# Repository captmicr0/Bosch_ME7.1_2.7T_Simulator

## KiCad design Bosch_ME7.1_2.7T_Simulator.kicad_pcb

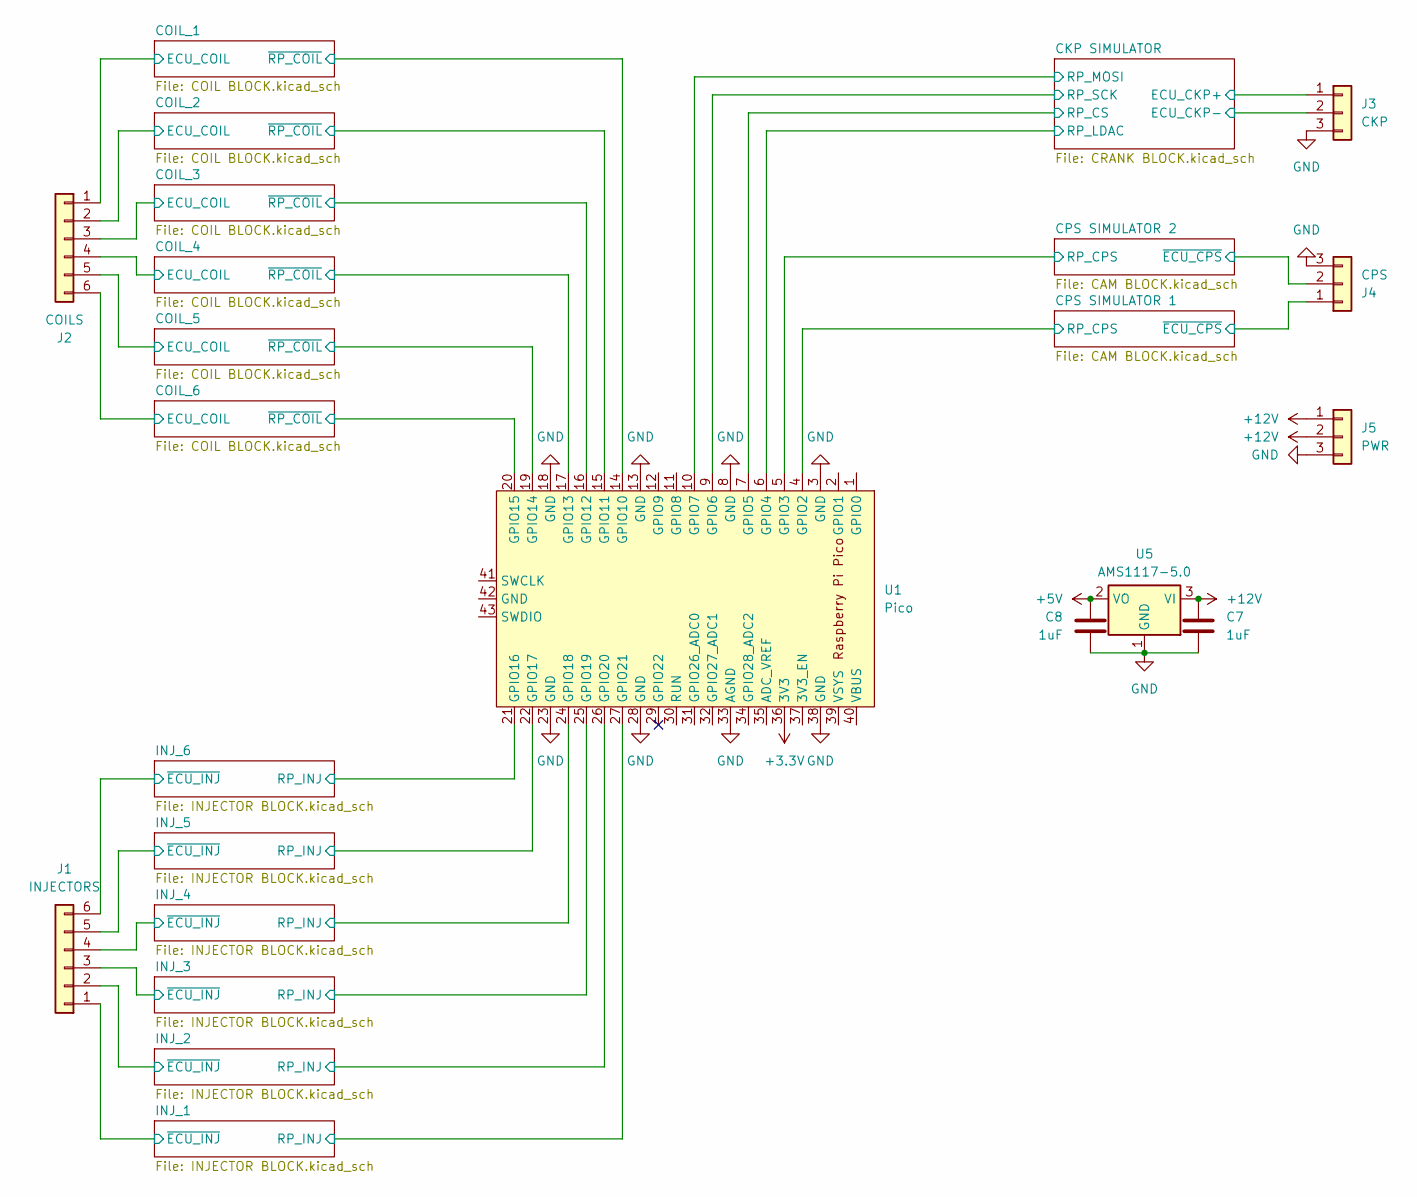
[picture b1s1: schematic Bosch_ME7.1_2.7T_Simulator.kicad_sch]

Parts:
C7, C8: 1uF; C_0603_1608Metric
J1: INJECTORS; JST_XH_B6B-XH-AM_1x06_P2.50mm_Vertical
J2: COILS; JST_XH_B6B-XH-AM_1x06_P2.50mm_Vertical
J3: CKP; JST_XH_B3B-XH-AM_1x03_P2.50mm_Vertical
J4: CPS; JST_XH_B3B-XH-AM_1x03_P2.50mm_Vertical
J5: PWR; JST_XH_B3B-XH-AM_1x03_P2.50mm_Vertical
U1: Pico; RPi_Pico_SMD_TH
U5: AMS1117-5.0; SOT-223-3_TabPin2

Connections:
+3.3V: U1.36 (3V3); also elsewhere on the board
+5V: C8.1, U5.2 (VO); also elsewhere on the board
+12V: C7.1, J5.1, J5.2, U5.3 (VI); also elsewhere on the board
/CKP SIMULATOR/ECU_CKP+: J3.1; also elsewhere on the board
/CKP SIMULATOR/ECU_CKP-: J3.2; also elsewhere on the board
/CKP SIMULATOR/RP_CS: U1.7 (GPIO5); also elsewhere on the board
/CKP SIMULATOR/RP_LDAC: U1.6 (GPIO4); also elsewhere on the board
/CKP SIMULATOR/RP_MOSI: U1.10 (GPIO7); also elsewhere on the board
/CKP SIMULATOR/RP_SCK: U1.9 (GPIO6); also elsewhere on the board
/COIL_1/ECU_COIL: J2.1; also elsewhere on the board
/COIL_1/~RP_COIL: U1.14 (GPIO10); also elsewhere on the board
/COIL_2/ECU_COIL: J2.2; also elsewhere on the board
/COIL_2/~RP_COIL: U1.15 (GPIO11); also elsewhere on the board
/COIL_3/ECU_COIL: J2.3; also elsewhere on the board
/COIL_3/~RP_COIL: U1.16 (GPIO12); also elsewhere on the board
/COIL_4/ECU_COIL: J2.4; also elsewhere on the board
/COIL_4/~RP_COIL: U1.17 (GPIO13); also elsewhere on the board
/COIL_5/ECU_COIL: J2.5; also elsewhere on the board
/COIL_5/~RP_COIL: U1.19 (GPIO14); also elsewhere on the board
/COIL_6/ECU_COIL: J2.6; also elsewhere on the board
/COIL_6/~RP_COIL: U1.20 (GPIO15); also elsewhere on the board
/CPS SIMULATOR 1/RP_CPS: U1.4 (GPIO2); also elsewhere on the board
/CPS SIMULATOR 1/~ECU_CPS: J4.1; also elsewhere on the board
/CPS SIMULATOR 2/RP_CPS: U1.5 (GPIO3); also elsewhere on the board
/CPS SIMULATOR 2/~ECU_CPS: J4.2; also elsewhere on the board
/INJ_1/RP_INJ: U1.27 (GPIO21); also elsewhere on the board
/INJ_1/~ECU_INJ: J1.1; also elsewhere on the board
/INJ_2/RP_INJ: U1.26 (GPIO20); also elsewhere on the board
/INJ_2/~ECU_INJ: J1.2; also elsewhere on the board
/INJ_3/RP_INJ: U1.25 (GPIO19); also elsewhere on the board
/INJ_3/~ECU_INJ: J1.3; also elsewhere on the board
/INJ_4/RP_INJ: U1.24 (GPIO18); also elsewhere on the board
/INJ_4/~ECU_INJ: J1.4; also elsewhere on the board
/INJ_5/RP_INJ: U1.22 (GPIO17); also elsewhere on the board
/INJ_5/~ECU_INJ: J1.5; also elsewhere on the board
/INJ_6/RP_INJ: U1.21 (GPIO16); also elsewhere on the board
/INJ_6/~ECU_INJ: J1.6; also elsewhere on the board
GND: C7.2, C8.2, J3.3, J4.3, J5.3, U1.3 (GND), U1.8 (GND), U1.13 (GND), U1.18 (GND), U1.23 (GND), U1.28 (GND), U1.33 (AGND), U1.38 (GND), U5.1 (GND); also elsewhere on the board

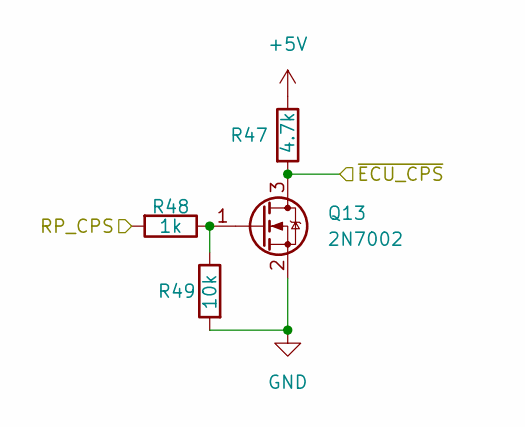
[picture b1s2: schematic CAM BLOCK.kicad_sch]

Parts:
Q13: 2N7002; SOT-23
R47: 4.7k; R_0603_1608Metric
R48: 1k; R_0603_1608Metric
R49: 10k; R_0603_1608Metric

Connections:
+5V: R47.1; also elsewhere on the board
/CPS SIMULATOR 1/RP_CPS: R48.2; also elsewhere on the board
/CPS SIMULATOR 1/~ECU_CPS: Q13.3 (D), R47.2; also elsewhere on the board
GND: Q13.2 (S), R49.2; also elsewhere on the board
unnamed: Q13.1 (G), R48.1, R49.1

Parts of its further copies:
Q14: 2N7002; SOT-23
R46: 4.7k; R_0603_1608Metric
R50: 1k; R_0603_1608Metric
R51: 10k; R_0603_1608Metric

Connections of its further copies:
+5V: R46.1; also elsewhere on the board
/CPS SIMULATOR 2/RP_CPS: R50.2; also elsewhere on the board
/CPS SIMULATOR 2/~ECU_CPS: Q14.3 (D), R46.2; also elsewhere on the board
GND: Q14.2 (S), R51.2; also elsewhere on the board
unnamed: Q14.1 (G), R50.1, R51.1

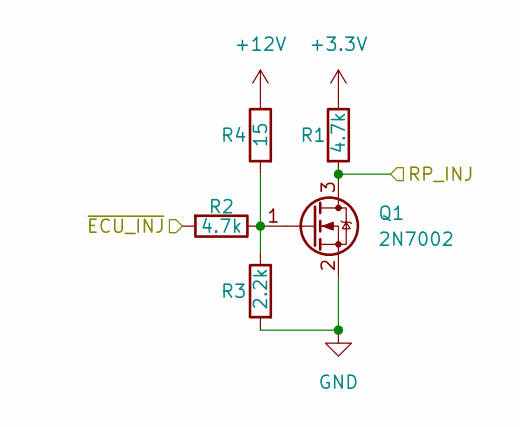
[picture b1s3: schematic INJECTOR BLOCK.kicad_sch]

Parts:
Q1: 2N7002; SOT-23
R1, R2: 4.7k; R_0603_1608Metric
R3: 2.2k; R_0603_1608Metric
R4: 15; JST_XH_B2B-XH-AM_1x02_P2.50mm_Vertical

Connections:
+3.3V: R1.1; also elsewhere on the board
+12V: R4.1; also elsewhere on the board
/INJ_1/RP_INJ: Q1.3 (D), R1.2; also elsewhere on the board
/INJ_1/~ECU_INJ: R2.2; also elsewhere on the board
GND: Q1.2 (S), R3.2; also elsewhere on the board
unnamed: Q1.1 (G), R2.1, R3.1, R4.2

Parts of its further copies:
Q4, Q6, Q8, Q10, Q12: 2N7002; SOT-23
R11, R18, R25, R32, R39: 15; JST_XH_B2B-XH-AM_1x02_P2.50mm_Vertical
R12, R13, R19, R20, R26, R27, R33, R34, R40, R41: 4.7k; R_0603_1608Metric
R14, R21, R28, R35, R42: 2.2k; R_0603_1608Metric

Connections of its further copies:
+3.3V: R12.1, R19.1, R26.1, R33.1, R40.1; also elsewhere on the board
+12V: R11.1, R18.1, R25.1, R32.1, R39.1; also elsewhere on the board
/INJ_2/RP_INJ: Q4.3 (D), R12.2; also elsewhere on the board
/INJ_2/~ECU_INJ: R13.2; also elsewhere on the board
/INJ_3/RP_INJ: Q6.3 (D), R19.2; also elsewhere on the board
/INJ_3/~ECU_INJ: R20.2; also elsewhere on the board
/INJ_4/RP_INJ: Q8.3 (D), R26.2; also elsewhere on the board
/INJ_4/~ECU_INJ: R27.2; also elsewhere on the board
/INJ_5/RP_INJ: Q10.3 (D), R33.2; also elsewhere on the board
/INJ_5/~ECU_INJ: R34.2; also elsewhere on the board
/INJ_6/RP_INJ: Q12.3 (D), R40.2; also elsewhere on the board
/INJ_6/~ECU_INJ: R41.2; also elsewhere on the board
GND: Q4.2 (S), Q6.2 (S), Q8.2 (S), Q10.2 (S), Q12.2 (S), R14.2, R21.2, R28.2, R35.2, R42.2; also elsewhere on the board
unnamed: Q4.1 (G), R11.2, R13.1, R14.1
unnamed: Q6.1 (G), R18.2, R20.1, R21.1
unnamed: Q8.1 (G), R25.2, R27.1, R28.1
unnamed: Q10.1 (G), R32.2, R34.1, R35.1
unnamed: Q12.1 (G), R39.2, R41.1, R42.1

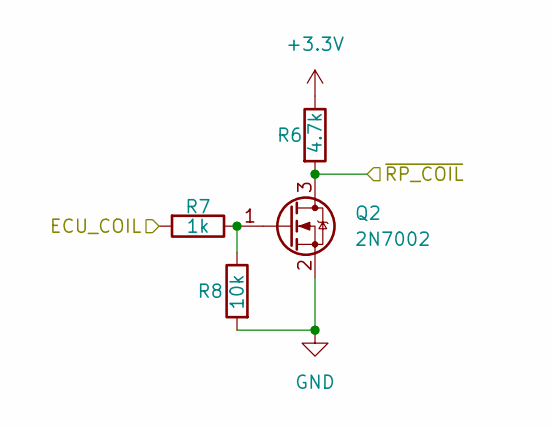
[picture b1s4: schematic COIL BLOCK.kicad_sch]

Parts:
Q2: 2N7002; SOT-23
R6: 4.7k; R_0603_1608Metric
R7: 1k; R_0603_1608Metric
R8: 10k; R_0603_1608Metric

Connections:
+3.3V: R6.1; also elsewhere on the board
/COIL_1/ECU_COIL: R7.2; also elsewhere on the board
/COIL_1/~RP_COIL: Q2.3 (D), R6.2; also elsewhere on the board
GND: Q2.2 (S), R8.2; also elsewhere on the board
unnamed: Q2.1 (G), R7.1, R8.1

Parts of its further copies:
Q3, Q5, Q7, Q9, Q11: 2N7002; SOT-23
R5, R15, R22, R29, R36: 4.7k; R_0603_1608Metric
R9, R16, R23, R30, R37: 1k; R_0603_1608Metric
R10, R17, R24, R31, R38: 10k; R_0603_1608Metric

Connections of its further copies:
+3.3V: R5.1, R15.1, R22.1, R29.1, R36.1; also elsewhere on the board
/COIL_2/ECU_COIL: R9.2; also elsewhere on the board
/COIL_2/~RP_COIL: Q3.3 (D), R5.2; also elsewhere on the board
/COIL_3/ECU_COIL: R16.2; also elsewhere on the board
/COIL_3/~RP_COIL: Q5.3 (D), R15.2; also elsewhere on the board
/COIL_4/ECU_COIL: R23.2; also elsewhere on the board
/COIL_4/~RP_COIL: Q7.3 (D), R22.2; also elsewhere on the board
/COIL_5/ECU_COIL: R30.2; also elsewhere on the board
/COIL_5/~RP_COIL: Q9.3 (D), R29.2; also elsewhere on the board
/COIL_6/ECU_COIL: R37.2; also elsewhere on the board
/COIL_6/~RP_COIL: Q11.3 (D), R36.2; also elsewhere on the board
GND: Q3.2 (S), Q5.2 (S), Q7.2 (S), Q9.2 (S), Q11.2 (S), R10.2, R17.2, R24.2, R31.2, R38.2; also elsewhere on the board
unnamed: Q3.1 (G), R9.1, R10.1
unnamed: Q5.1 (G), R16.1, R17.1
unnamed: Q7.1 (G), R23.1, R24.1
unnamed: Q9.1 (G), R30.1, R31.1
unnamed: Q11.1 (G), R37.1, R38.1

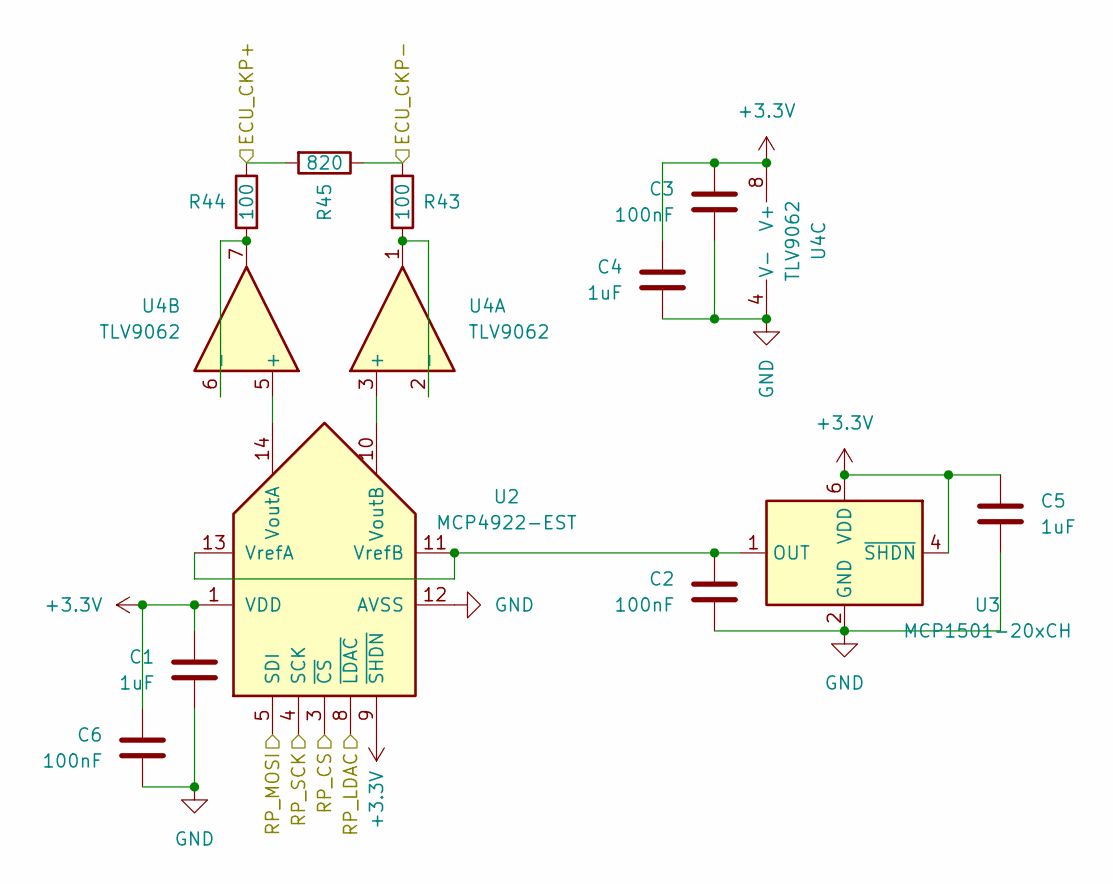
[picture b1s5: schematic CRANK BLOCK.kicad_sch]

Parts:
C1, C4, C5: 1uF; C_0603_1608Metric
C2, C3, C6: 100nF; C_0603_1608Metric
R43, R44: 100; R_0603_1608Metric
R45: 820; R_0603_1608Metric
U2: MCP4922-EST; TSSOP-14_4.4x5mm_P0.65mm
U3: MCP1501-20xCH; SOT-23-6
U4: TLV9062; TSSOP-8_4.4x3mm_P0.65mm

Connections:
+3.3V: C1.1, C3.1, C4.1, C5.1, C6.1, U2.1 (VDD), U2.9 (~SHDN), U3.4 (~SHDN), U3.6 (VDD), U4.8 (V+); also elsewhere on the board
/CKP SIMULATOR/ECU_CKP+: R44.1, R45.2; also elsewhere on the board
/CKP SIMULATOR/ECU_CKP-: R43.1, R45.1; also elsewhere on the board
/CKP SIMULATOR/RP_CS: U2.3 (~CS); also elsewhere on the board
/CKP SIMULATOR/RP_LDAC: U2.8 (~LDAC); also elsewhere on the board
/CKP SIMULATOR/RP_MOSI: U2.5 (SDI); also elsewhere on the board
/CKP SIMULATOR/RP_SCK: U2.4 (SCK); also elsewhere on the board
GND: C1.2, C2.2, C3.2, C4.2, C5.2, C6.2, U2.12 (AVSS), U3.2 (GND), U3.3 (GND), U3.5 (GND), U4.4 (V-); also elsewhere on the board
unnamed: U2.14 (VoutA), U4.5 (+)
unnamed: U2.10 (VoutB), U4.3 (+)
unnamed: C2.1, U2.11 (VrefB), U2.13 (VrefA), U3.1 (OUT)
unnamed: R43.2, U4.1, U4.2 (-)
unnamed: R44.2, U4.6 (-), U4.7

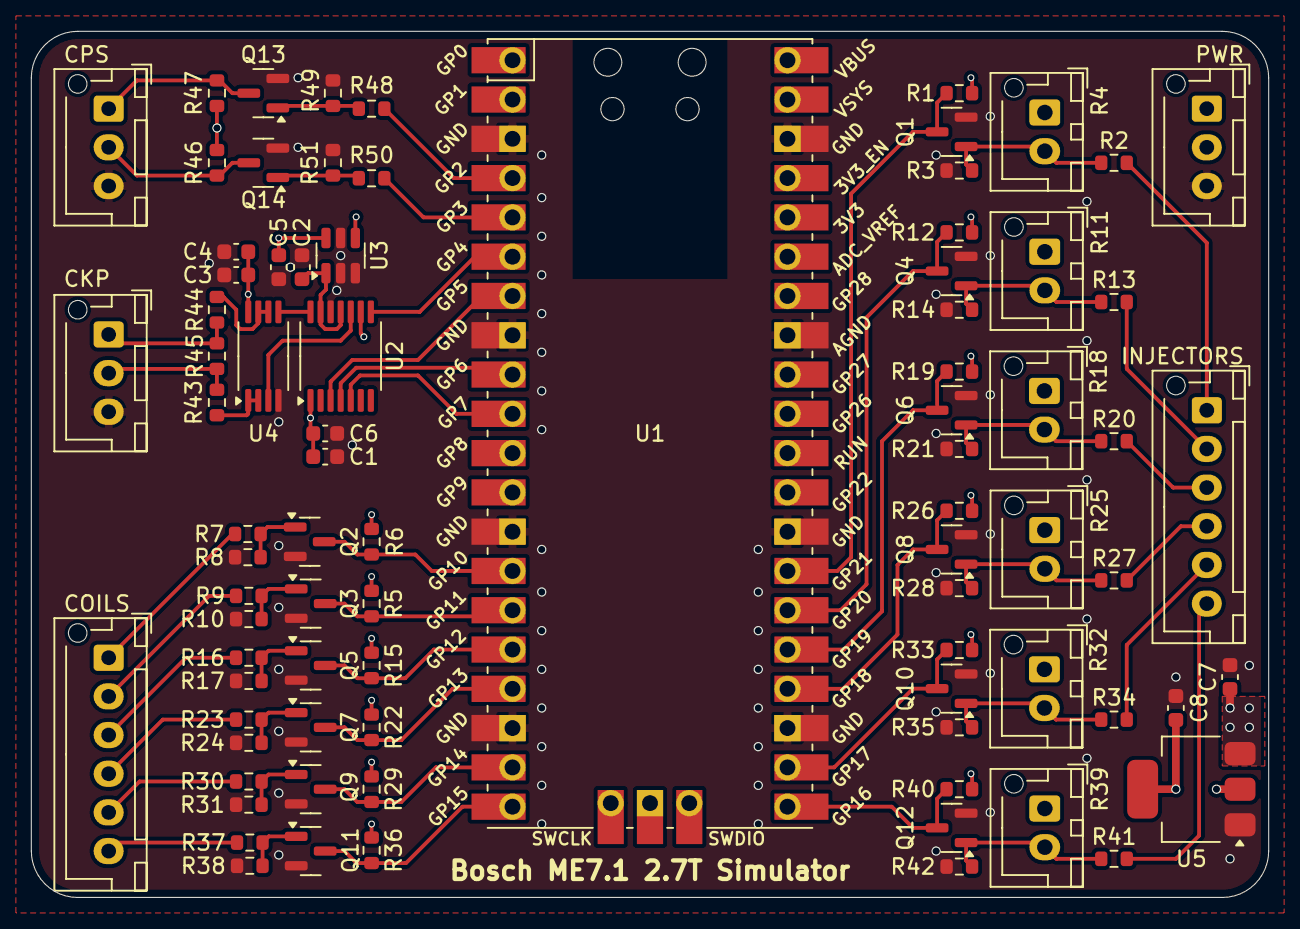
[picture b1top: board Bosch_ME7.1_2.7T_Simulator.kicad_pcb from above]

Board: 4 copper layers, 80.0 x 56.0 mm, 83 parts (0 on the bottom side), 57 nets.

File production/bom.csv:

Designator,Footprint,Quantity,Value,LCSC Part #
"C1, C4, C5, C7, C8",0603,5,1uF,
"C2, C3, C6",0603,3,100nF,
J1,JST_XH_B6B-XH-AM_1x06_P2.50mm_Vertical,1,INJECTORS,
J2,JST_XH_B6B-XH-AM_1x06_P2.50mm_Vertical,1,COILS,
J3,JST_XH_B3B-XH-AM_1x03_P2.50mm_Vertical,1,CKP,
J4,JST_XH_B3B-XH-AM_1x03_P2.50mm_Vertical,1,CPS,
J5,JST_XH_B3B-XH-AM_1x03_P2.50mm_Vertical,1,PWR,
"Q1, Q10, Q11, Q12, Q13, Q14, Q2, Q3, Q4, Q5, Q6, Q7, Q8, Q9",SOT-23,14,2N7002,
"R1, R12, R13, R15, R19, R2, R20, R22, R26, R27, R29, R33, R34, R36, R40, R41, R46, R47, R5, R6",0603,20,4.7k,
"R10, R17, R24, R31, R38, R49, R51, R8",0603,8,10k,
"R11, R18, R25, R32, R39, R4",JST_XH_B2B-XH-AM_1x02_P2.50mm_Vertical,6,15,
"R14, R21, R28, R3, R35, R42",0603,6,2.2k,
"R16, R23, R30, R37, R48, R50, R7, R9",0603,8,1k,
"R43, R44",0603,2,100,
R45,0603,1,820,
U1,RPi_Pico_SMD_TH,1,Pico,
U2,TSSOP-14_4.4x5mm_P0.65mm,1,MCP4922-EST,
U3,SOT-23-6,1,MCP1501-20xCH,
U4,TSSOP-8_4.4x3mm_P0.65mm,1,TLV9062,
U5,SOT-223-3_TabPin2,1,AMS1117-5.0,
